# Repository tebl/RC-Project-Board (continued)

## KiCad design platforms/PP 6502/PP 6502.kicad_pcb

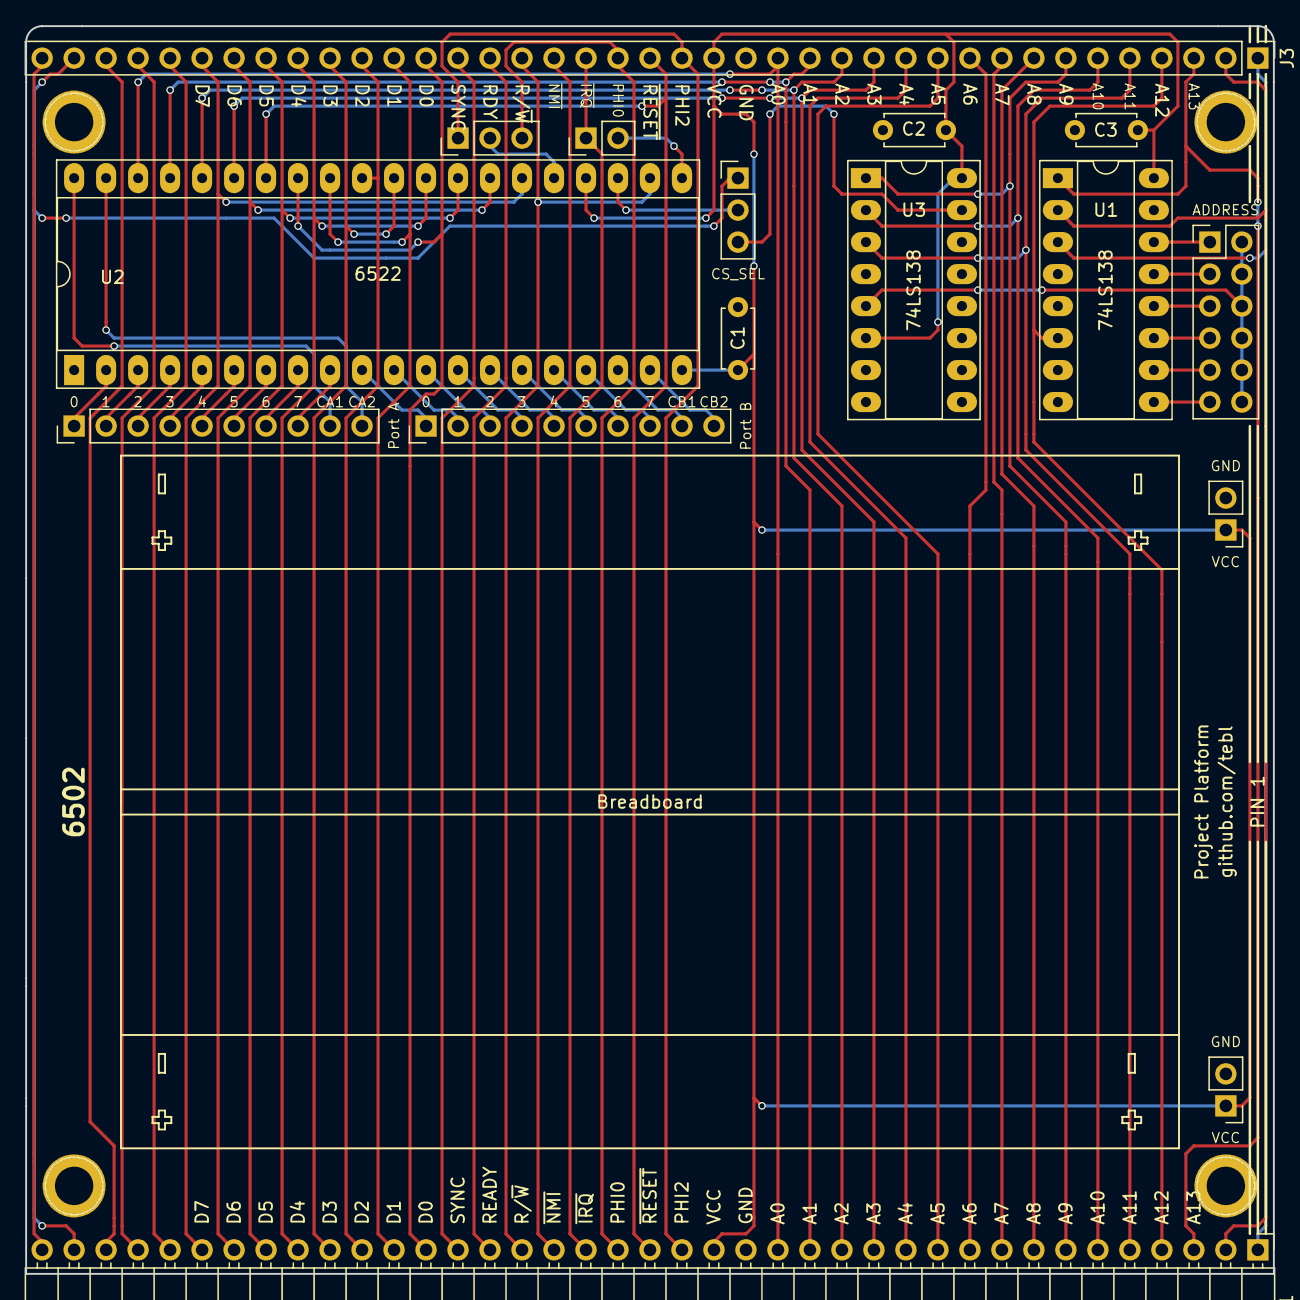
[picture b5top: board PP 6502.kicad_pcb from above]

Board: 2 copper layers, 99.1 x 99.1 mm, 21 parts (0 on the bottom side), 70 nets.

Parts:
BB1: Breadboard; RND 255-00005
C1, C2, C3: 100nF; C_Disc_D4.7mm_W2.5mm_P5.00mm
J1: Signals; Pin_Header_Angled_1x39_Pitch2.54mm
J3: SBC; Pin_Header_Straight_1x39_Pitch2.54mm
J4: ADDRESS; Pin_Header_Straight_2x06_Pitch2.54mm
J5: Port A; Pin_Header_Straight_1x10_Pitch2.54mm
J6: Port B; Pin_Header_Straight_1x10_Pitch2.54mm
J7: PWR1; Pin_Header_Straight_1x02_Pitch2.54mm
J8: PWR2; Pin_Header_Straight_1x02_Pitch2.54mm
JP1: VIA_IRQ; Pin_Header_Straight_1x02_Pitch2.54mm
JP2: CS_SEL; Pin_Header_Straight_1x03_Pitch2.54mm
JP3: VIA_CLK; Pin_Header_Straight_1x03_Pitch2.54mm
M1, M2, M3, M4: Mounting; 1pin
U1, U3: 74LS138; DIP-16_W7.62mm_Socket_LongPads
U2: 6522; DIP-40_W15.24mm_Socket_LongPads

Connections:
/4K3: J4.1, U1.14
/4K5: J4.3, U1.13
/4K7: J4.5, U1.12
/4K9: J4.7, U1.11
/4KB: J4.9, U1.10
/4KD: J4.11, U1.9
/A0: J1.16, J3.16, U2.38
/A1: J1.15, J3.15, U2.37
/A2: J1.14, J3.14, U2.36
/A3: J1.13, J3.13, U2.35
/A4: J1.12, J3.12
/A5: J1.11, J3.11
/A6: J1.10, J3.10
/A7: J1.9, J3.9
/A8: J1.8, J3.8
/A9: J1.7, J3.7, U3.1
/A10: J1.6, J3.6, U3.2
/A11: J1.5, J3.5, U3.3
/A12: J1.4, J3.4, U1.6
/A13: J1.3, J3.3, U1.1
/A14: J1.2, J3.2, U1.2
/A15: J1.1, J3.1, U1.3
/D0: J1.27, J3.27, U2.33
/D1: J1.28, J3.28, U2.32
/D2: J1.29, J3.29, U2.31
/D3: J1.30, J3.30, U2.30
/D4: J1.31, J3.31, U2.29
/D5: J1.32, J3.32, U2.28
/D6: J1.33, J3.33, U2.27
/D7: J1.34, J3.34, U2.26
/PHI0: J1.21, J3.21, JP3.3
/PHI2: J1.19, J3.19, JP3.1
/PIN35: J1.35, J3.35
/PIN36: J1.36, J3.36
/PIN37: J1.37, J3.37
/PIN39: J1.39, J3.39
/R/~W: J1.24, J3.24, U2.22
/SYNC: J1.26, J3.26
/~IO3: J1.38, J3.38, JP2.1
/~IRQ: J1.22, J3.22, JP1.1
/~NMI: J1.23, J3.23
/~RDY: J1.25, J3.25
/~RESET: J1.20, J3.20, U2.34
GND: C1.2, C2.2, C3.2, J1.17, J3.17, J7.2, J8.2, U1.4, U1.5, U1.8, U2.1, U3.4, U3.8
unnamed: J4.2, J4.4, J4.6, J4.8, J4.10, J4.12, U3.5
unnamed: J5.1, U2.2
unnamed: J5.2, U2.3
unnamed: J5.3, U2.4
unnamed: J5.4, U2.5
unnamed: J5.5, U2.6
unnamed: J5.6, U2.7
unnamed: J5.7, U2.8
unnamed: J5.8, U2.9
unnamed: J5.9, U2.40
unnamed: J5.10, U2.39
unnamed: J6.1, U2.10
unnamed: J6.2, U2.11
unnamed: J6.3, U2.12
unnamed: J6.4, U2.13
unnamed: J6.5, U2.14
unnamed: J6.6, U2.15
unnamed: J6.7, U2.16
unnamed: J6.8, U2.17
unnamed: J6.9, U2.18
unnamed: J6.10, U2.19
unnamed: JP1.2, U2.21
unnamed: JP2.3, U3.15
unnamed: JP3.2, U2.25
VCC: C1.1, C2.1, C3.1, J1.18, J3.18, J7.1, J8.1, U1.16, U2.20, U2.24, U3.6, U3.16
~6522_CS: JP2.2, U2.23

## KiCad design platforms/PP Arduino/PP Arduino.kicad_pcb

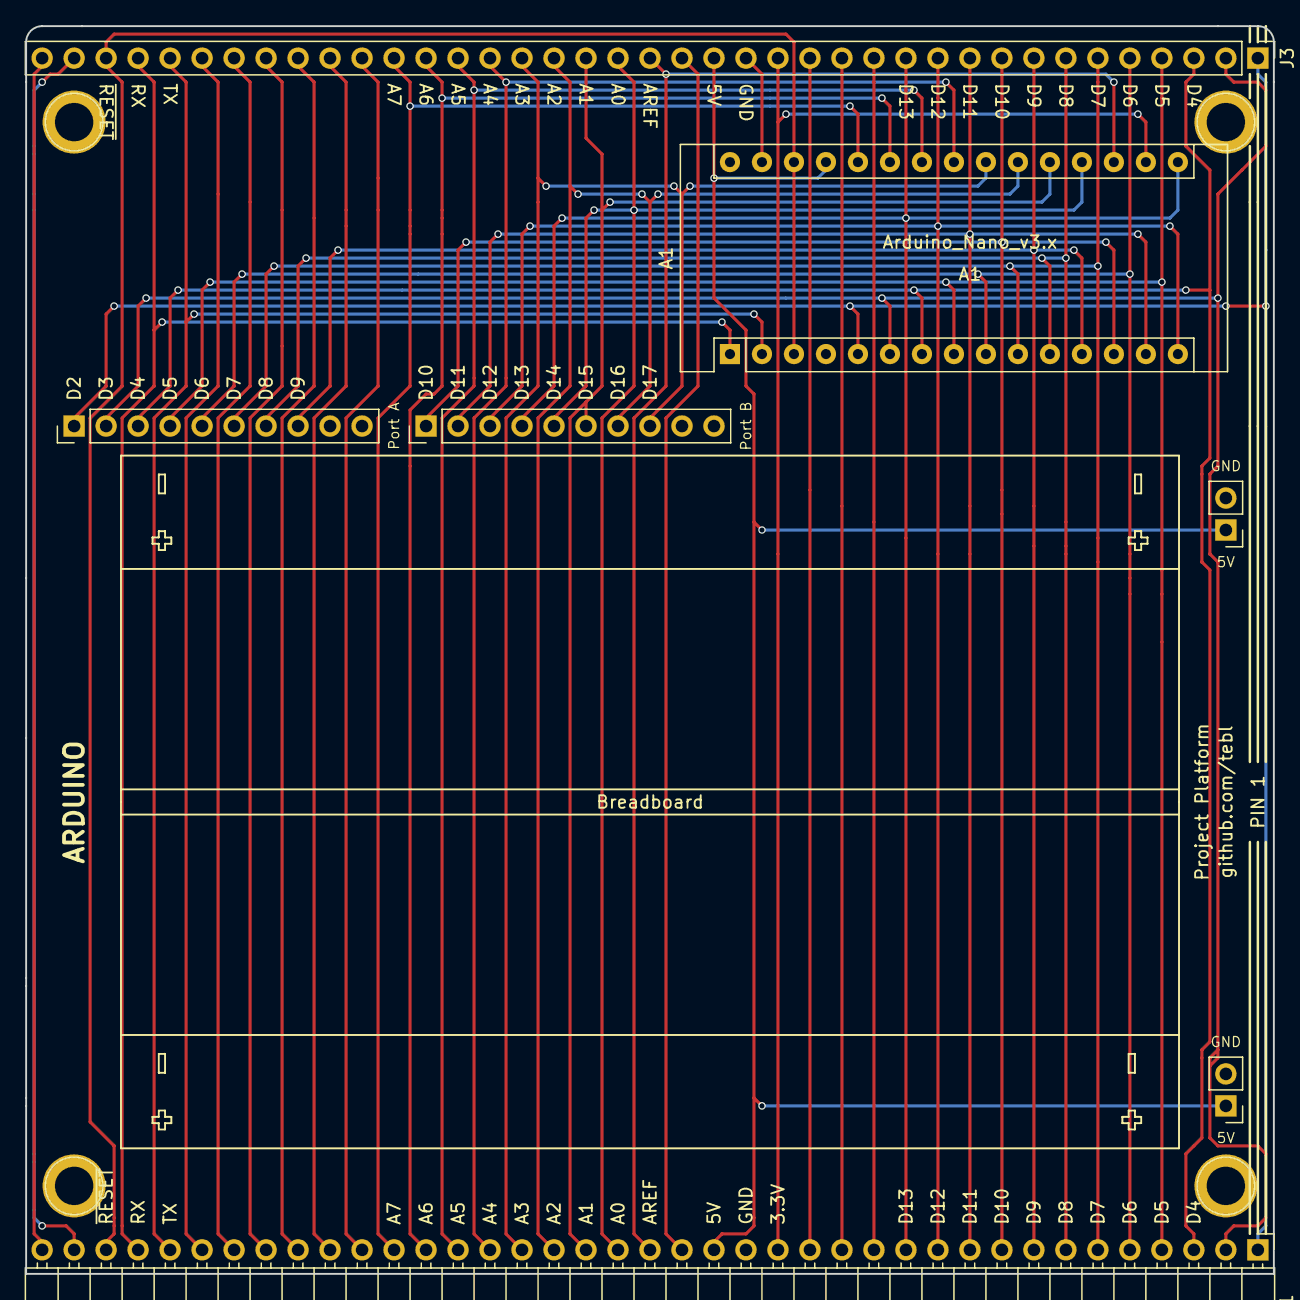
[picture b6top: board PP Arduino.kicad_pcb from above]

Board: 2 copper layers, 99.1 x 99.1 mm, 12 parts (0 on the bottom side), 39 nets.

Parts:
A1: Arduino_Nano_v3.x; Arduino_Nano
BB1: Breadboard; RND 255-00005
J1: Signals; Pin_Header_Angled_1x39_Pitch2.54mm
J3: SBC; Pin_Header_Straight_1x39_Pitch2.54mm
J5: Port A; Pin_Header_Straight_1x10_Pitch2.54mm
J6: Port B; Pin_Header_Straight_1x10_Pitch2.54mm
J7: PWR1; Pin_Header_Straight_1x02_Pitch2.54mm
J8: PWR2; Pin_Header_Straight_1x02_Pitch2.54mm
M1, M2, M3, M4: Mounting; 1pin

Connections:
+3V3: A1.17, J1.16, J3.16
/A0: A1.19, J1.21, J3.21, J6.5
/A1: A1.20, J1.22, J3.22, J6.6
/A2: A1.21, J1.23, J3.23, J6.7
/A3: A1.22, J1.24, J3.24, J6.8
/A4: A1.23, J1.25, J3.25
/A5: A1.24, J1.26, J3.26
/A6: A1.25, J1.27, J3.27
/A7: A1.26, J1.28, J3.28
/AREF: A1.18, J1.20, J3.20
/D2: A1.5, J1.1, J3.1, J5.1
/D3: A1.6, J1.2, J3.2, J5.2
/D4: A1.7, J1.3, J3.3, J5.3
/D5: A1.8, J1.4, J3.4, J5.4
/D6: A1.9, J1.5, J3.5, J5.5
/D7: A1.10, J1.6, J3.6, J5.6
/D8: A1.11, J1.7, J3.7, J5.7
/D9: A1.12, J1.8, J3.8, J5.8
/D10: A1.13, J1.9, J3.9, J6.1
/D11: A1.14, J1.10, J3.10, J6.2
/D12: A1.15, J1.11, J3.11, J6.3
/D13: A1.16, J1.12, J3.12, J6.4
/PIN13: J1.13, J3.13
/PIN14: J1.14, J3.14
/PIN15: J1.15, J3.15
/PIN19: J1.19, J3.19
/PIN29: J1.29, J3.29
/PIN30: J1.30, J3.30
/PIN31: J1.31, J3.31
/PIN32: J1.32, J3.32
/PIN33: J1.33, J3.33
/PIN34: J1.34, J3.34
/PIN38: J1.38, J3.38
/PIN39: J1.39, J3.39
/RX: A1.1, J1.36, J3.36
/TX: A1.2, J1.35, J3.35
/~RESET: A1.3, A1.28, J1.37, J3.37
GND: A1.4, A1.29, J1.17, J3.17, J7.2, J8.2
VCC: A1.27, J1.18, J3.18, J7.1, J8.1

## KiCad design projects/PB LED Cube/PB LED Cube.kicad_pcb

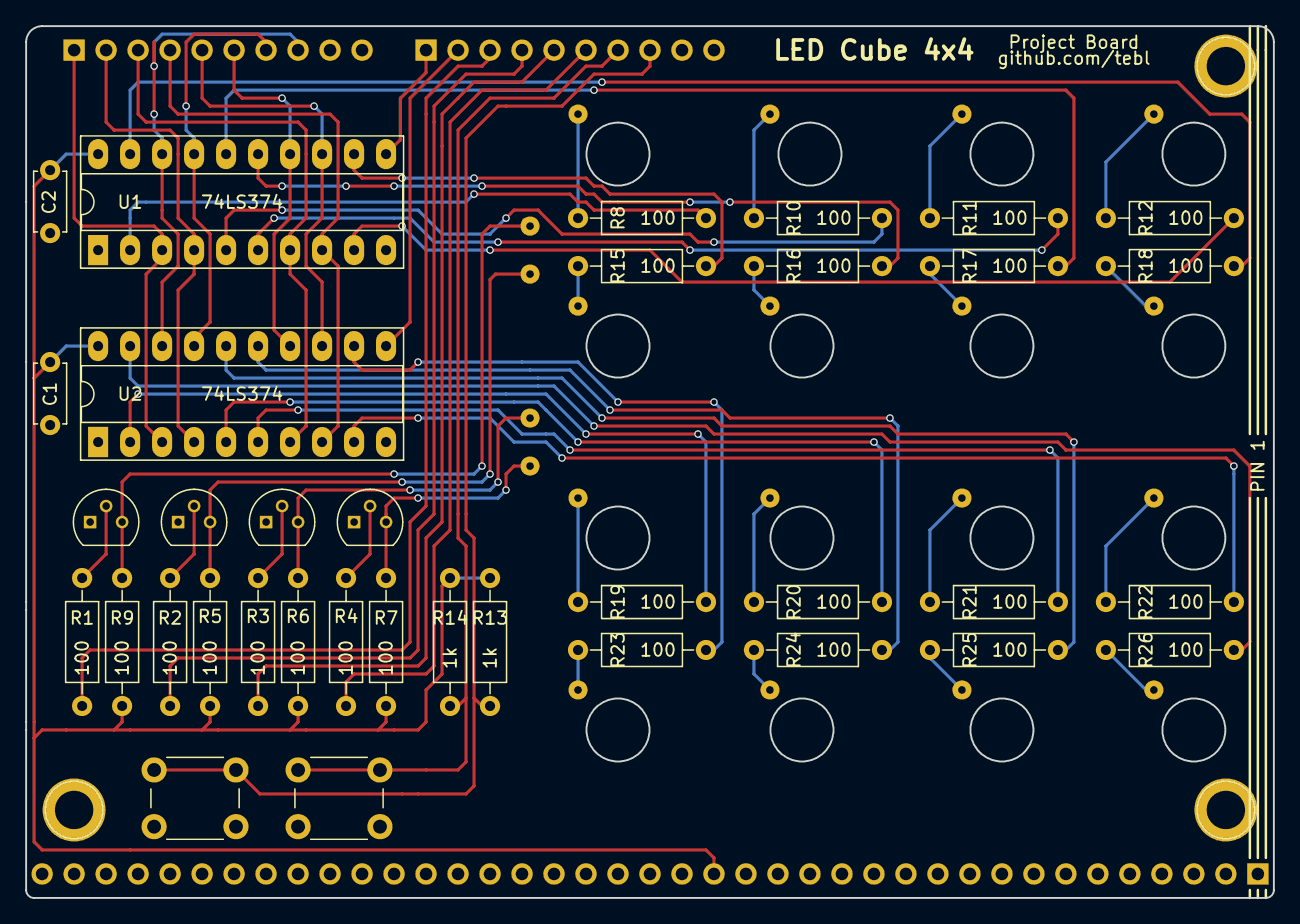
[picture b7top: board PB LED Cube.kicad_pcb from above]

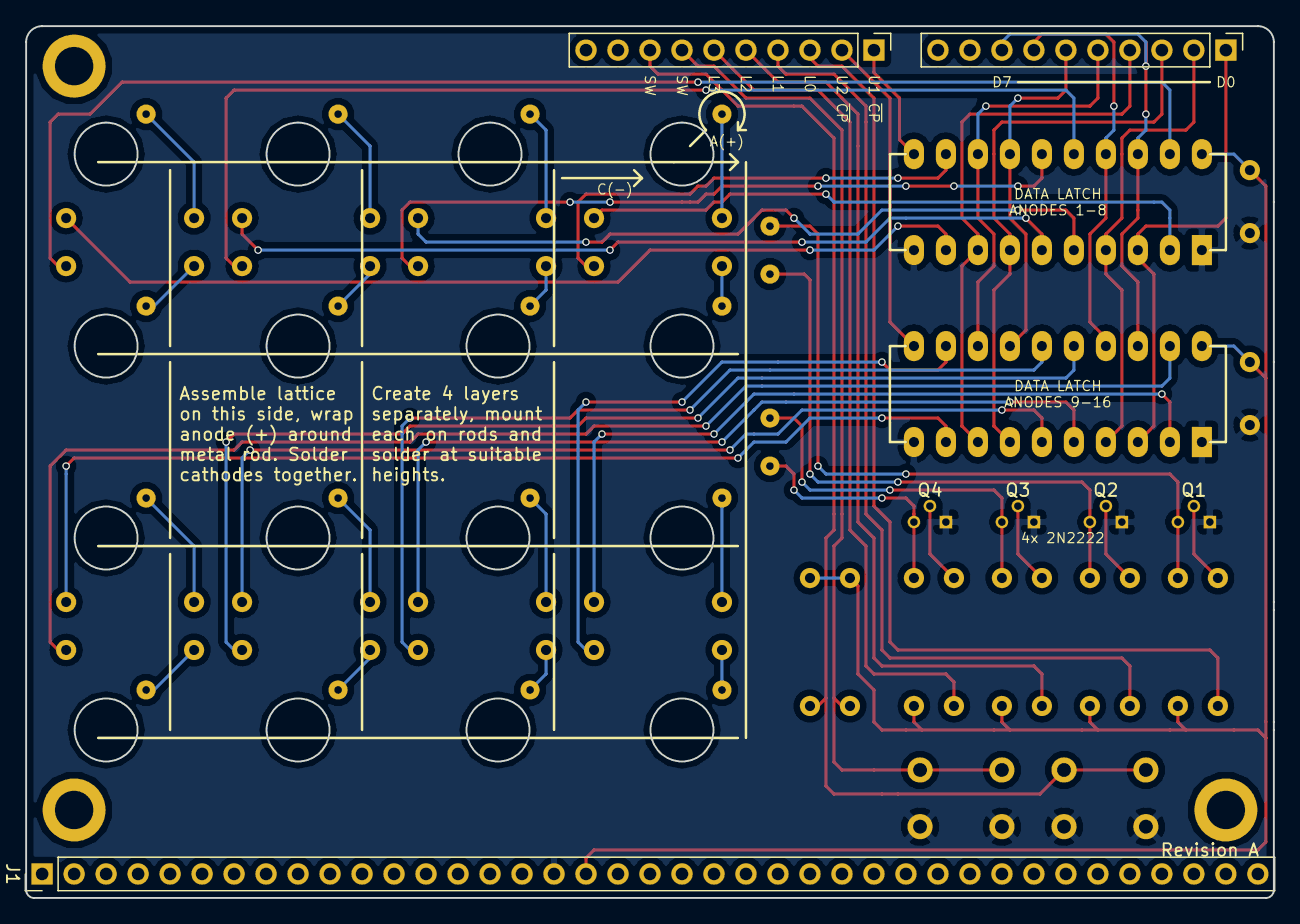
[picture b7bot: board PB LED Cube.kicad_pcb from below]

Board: 2 copper layers, 99.1 x 69.2 mm, 43 parts (3 on the bottom side), 58 nets.

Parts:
A1: LED_Cube_4x4
C1, C2: 100nF; C_Disc_D4.7mm_W2.5mm_P5.00mm
J1: Signals; Pin_Header_Straight_1x39_Pitch2.54mm
J5: Port A; Pin_Header_Straight_1x10_Pitch2.54mm
J6: Port B; Pin_Header_Straight_1x10_Pitch2.54mm
M1, M2, M3: Mounting; 1pin
Q1, Q2, Q3, Q4: PN2222A; TO-92_Molded_Narrow
R1, R2, R3, R4, R5, R6, R7, R8, R9, R10, R11, R12, R15, R16, R17, R18, R19, R20, R21, R22, R23, R24, R25, R26: 100; R_Axial_DIN0207_L6.3mm_D2.5mm_P10.16mm_Horizontal
R13, R14: 1k; R_Axial_DIN0207_L6.3mm_D2.5mm_P10.16mm_Horizontal
SW1, SW2: SW_Push; SW_PUSH_6mm
U1, U2: 74LS374; DIP-20_W7.62mm_Socket_LongPads

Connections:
/PA0: J5.1, U1.3, U2.3
/PA1: J5.2, U1.4, U2.4
/PA2: J5.3, U1.7, U2.7
/PA3: J5.4, U1.8, U2.8
/PA4: J5.5, U1.13, U2.13
/PA5: J5.6, U1.14, U2.14
/PA6: J5.7, U1.17, U2.17
/PA7: J5.8, U1.18, U2.18
/PB0: J6.1, U1.11
/PB1: J6.2, U2.11
/PB2: J6.3, R1.2
/PB3: J6.4, R2.2
/PB4: J6.5, R3.2
/PB5: J6.6, R4.2
/PB6: J6.7, R14.1, SW2.1
/PB7: J6.8, R13.1, SW1.1
GND: C1.2, C2.2, J1.17, Q1.1, Q2.1, Q3.1, Q4.1, SW1.2, SW2.2, U1.1, U1.10, U2.1, U2.10
unnamed: A1.1, R8.1
unnamed: A1.2, R10.1
unnamed: A1.3, R11.1
unnamed: A1.4, R12.1
unnamed: A1.5, R15.1
unnamed: A1.6, R16.1
unnamed: A1.7, R17.1
unnamed: A1.8, R18.1
unnamed: A1.9, R19.1
unnamed: A1.10, R20.1
unnamed: A1.11, R21.1
unnamed: A1.12, R22.1
unnamed: A1.13, R23.1
unnamed: A1.14, R24.1
unnamed: A1.15, R25.1
unnamed: A1.16, R26.1
unnamed: A1.17, Q1.3, R9.1
unnamed: A1.18, Q2.3, R5.1
unnamed: A1.19, Q3.3, R6.1
unnamed: A1.20, Q4.3, R7.1
unnamed: Q1.2, R1.1
unnamed: Q2.2, R2.1
unnamed: Q3.2, R3.1
unnamed: Q4.2, R4.1
unnamed: R8.2, U1.2
unnamed: R10.2, U1.5
unnamed: R11.2, U1.6
unnamed: R12.2, U1.9
unnamed: R15.2, U1.12
unnamed: R16.2, U1.15
unnamed: R17.2, U1.16
unnamed: R18.2, U1.19
unnamed: R19.2, U2.2
unnamed: R20.2, U2.5
unnamed: R21.2, U2.6
unnamed: R22.2, U2.9
unnamed: R23.2, U2.12
unnamed: R24.2, U2.15
unnamed: R25.2, U2.16
unnamed: R26.2, U2.19
VCC: C1.1, C2.1, J1.18, R5.2, R6.2, R7.2, R9.2, R13.2, R14.2, U1.20, U2.20

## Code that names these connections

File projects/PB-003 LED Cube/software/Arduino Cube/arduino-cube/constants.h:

#define PA0 2
#define PA1 3
#define PA2 4
#define PA3 5
#define PA4 6
#define PA5 7
#define PA6 8
#define PA7 9
#define PB0 10
#define PB1 11
#define PB2 12
#define PB3 13
#define PB4 A0
#define PB5 A1
#define PB6 A2
#define PB7 A3

#define CP1 PB0
#define CP2 PB1
#define L0 PB2
#define L1 PB3
#define L2 PB4
#define L3 PB5
#define SW2 PB6
#define SW1 PB7

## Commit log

2019-12-29 Covox Sound board
2019-12-30 Added 6502 Project Platform Board
2019-12-31 Moved into this repository
2019-12-31 Moved LED cube here as well
2019-12-31 Reorganized libraries
2020-01-10 Added Arduino platform board
2020-01-10 Silkscreen tweaks
2020-01-10 Moved things around
2020-01-10 Gallery images
2020-01-11 README
2020-01-23 Fixed 6502 address calculations
2020-01-25 Make a tone
2020-01-27 Backplane extension
2020-02-05 Game board base
2020-02-06 Gameboard faceplate layout and logo
2020-02-14 Gerber export
2020-02-14 PB-003 kicad5 update
2020-02-28 Added some pictures
2020-02-28 Game board pictures
2020-02-28 GB-001 README
2020-02-29 6502 games chapter 01 and 02
2020-02-29 Chapter 3
2020-02-29 Build for BE6502
2020-02-29 Hexguess
2020-03-02 Chapter 5
2020-03-03 HEX files now actually Intel Hex files
2020-03-03 Fixed readkey
2020-03-03 Fixed music (accidentally overwrote keyboard routines)
2020-03-03 RC-ONE README
2020-03-04 Chapter 6
2020-03-07 Chapter 7
2020-03-14 Arduino gerber export
2020-03-14 Updated chapter 7
2020-03-21 Chapter 9
2020-04-20 TODO document
2020-05-21 Arduino LED cube sketch
2020-10-11 Added IRQ pin to 6502 Game Board
2020-10-11 Changed covox speaker amplification circuit
2020-11-02 Moved game board IRQ connection to correct VIA
2021-01-25 Added pictures
